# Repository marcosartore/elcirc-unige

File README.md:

# elcirc-unige
This repository contains public domain contents of the Electronics and Circuits Ph.D. course @UniGe held by Marco Sartore.

The folder "analog-pid" contains the Kicad project of an Analog PID (Proportional Integral Derivative) controller.
Production files are in the "gerber" subfolder.

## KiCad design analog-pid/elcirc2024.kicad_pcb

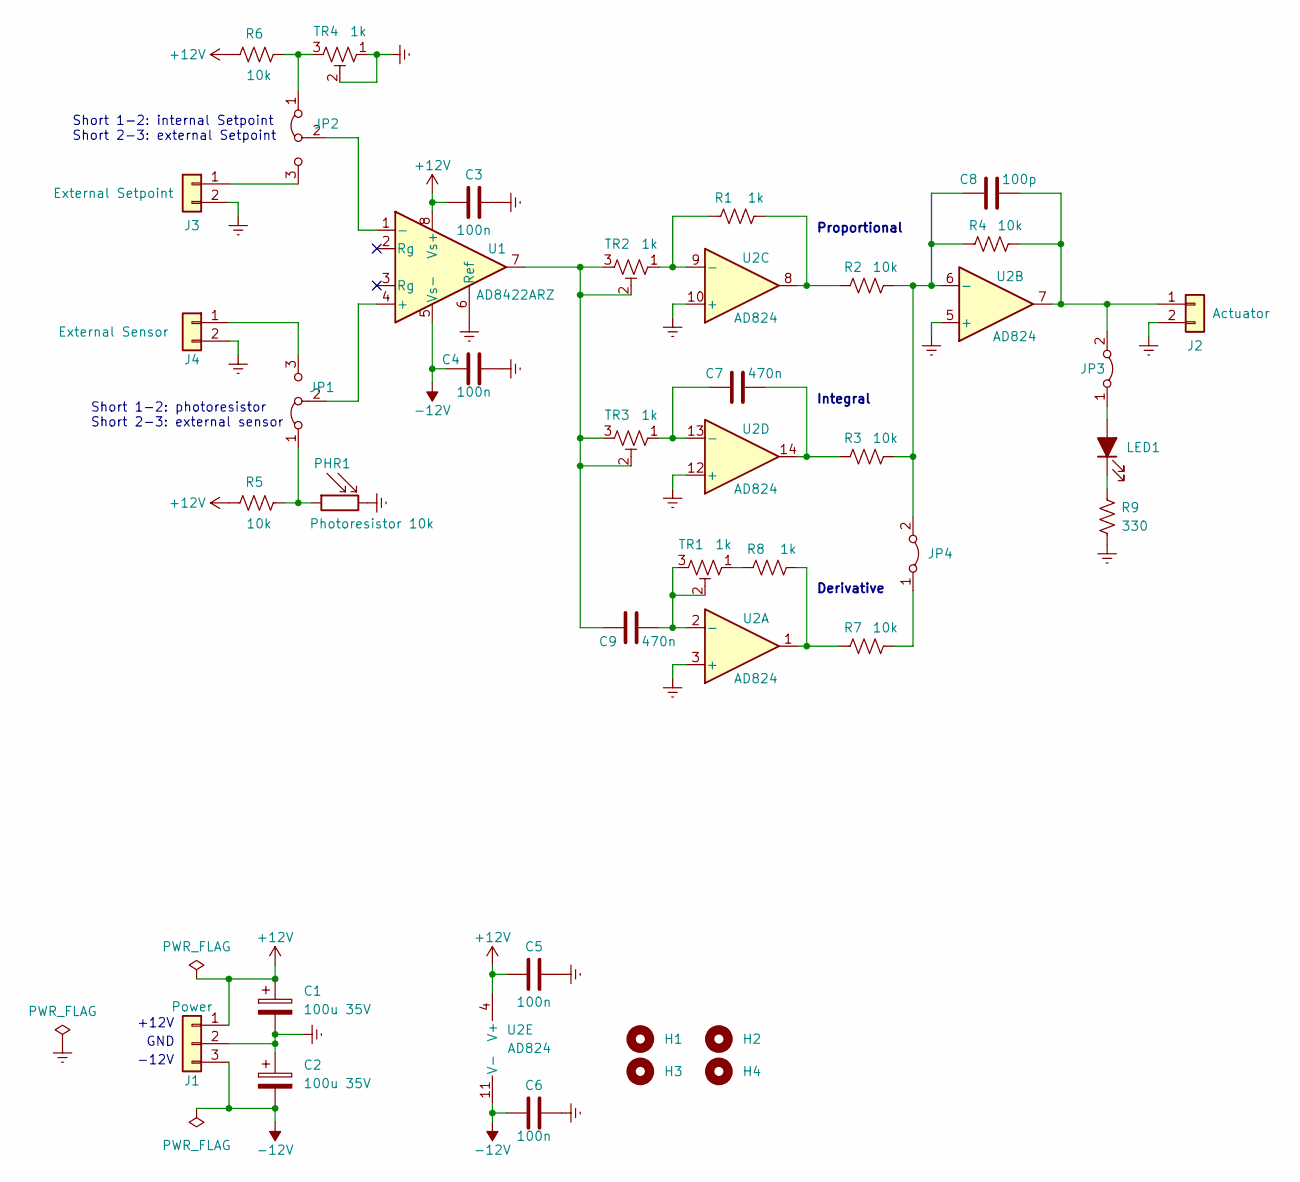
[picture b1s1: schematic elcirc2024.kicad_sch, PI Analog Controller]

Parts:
C1, C2: 100u 35V; CP_Elec_6.3x7.7
C3, C4, C5, C6: 100n; C_0805_2012Metric_Pad1.18x1.45mm_HandSolder
C7, C9: 470n; C_0805_2012Metric_Pad1.18x1.45mm_HandSolder
C8: 100p; C_0805_2012Metric_Pad1.18x1.45mm_HandSolder
H1, H2, H3, H4: MountingHole; MountingHole_3.2mm_M3
J1: Power; TerminalBlock_Phoenix_PT-1,5-3-3.5-H_1x03_P3.50mm_Horizontal; Digikey A112369-ND
J2: Actuator; conn_TE_282834-2; Digikey A98333-ND
J3: External Setpoint; conn_TE_282834-2; Digikey A98333-ND
J4: External Sensor; conn_TE_282834-2; Digikey A98333-ND
JP1, JP2: Jumper_3_Bridged12; PinHeader_1x03_P2.54mm_Vertical
JP3, JP4: Jumper_2_Bridged; PinHeader_1x02_P2.54mm_Vertical
LED1: LED_Filled; LED_D5.0mm
PHR1: Photoresistor 10k; photoresistor_NSL-5152
R1, R8: 1k; R_0805_2012Metric_Pad1.20x1.40mm_HandSolder
R2, R3, R4, R5, R6, R7: 10k; R_0805_2012Metric_Pad1.20x1.40mm_HandSolder
R9: 330; R_0805_2012Metric_Pad1.20x1.40mm_HandSolder
TR1, TR2, TR3, TR4: 1k; Potentiometer_Bourns_3296W_Vertical
U1: AD8422ARZ; SOIC-8_3.9x4.9mm_P1.27mm
U2: AD824; SOIC-14_3.9x8.7mm_P1.27mm

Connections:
+12V: C1.1, C3.1, C5.1, J1.1, R5.2, R6.2, U1.8 (Vs+), U2.4 (V+)
-12V: C2.2, C4.1, C6.1, J1.3, U1.5 (Vs-), U2.11 (V-)
GNDREF: C1.2, C2.1, C3.2, C4.2, C5.2, C6.2, J1.2, J2.2, J3.2, J4.2, PHR1.2, R9.1, TR4.1, TR4.2, U1.6 (Ref), U2.3 (+), U2.5 (+), U2.10 (+), U2.12 (+)
unnamed: C7.2, R3.1, U2.14
unnamed: C9.1, TR2.2, TR2.3, TR3.2, TR3.3, U1.7
unnamed: C8.2, J2.1, JP3.2 (B), R4.2, U2.7
unnamed: J3.1, JP2.3 (B)
unnamed: J4.1, JP1.3 (B)
unnamed: JP1.1 (A), PHR1.1, R5.1
unnamed: JP1.2 (C), U1.4 (+)
unnamed: JP2.1 (A), R6.1, TR4.3
unnamed: JP2.2 (C), U1.1 (-)
unnamed: JP3.1 (A), LED1.2 (A)
unnamed: JP4.1 (A), R7.2
unnamed: C8.1, JP4.2 (B), R2.2, R3.2, R4.1, U2.6 (-)
unnamed: LED1.1 (K), R9.2
unnamed: R1.2, R2.1, U2.8
unnamed: R7.1, R8.2, U2.1
unnamed: R8.1, TR1.1
unnamed: C9.2, TR1.2, TR1.3, U2.2 (-)
unnamed: R1.1, TR2.1, U2.9 (-)
unnamed: C7.1, TR3.1, U2.13 (-)

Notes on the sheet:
Short 1-2: internal Setpoint Short 2-3: external Setpoint
Integral
GND
Derivative
+12V
Short 1-2: photoresistor Short 2-3: external sensor
-12V
Proportional

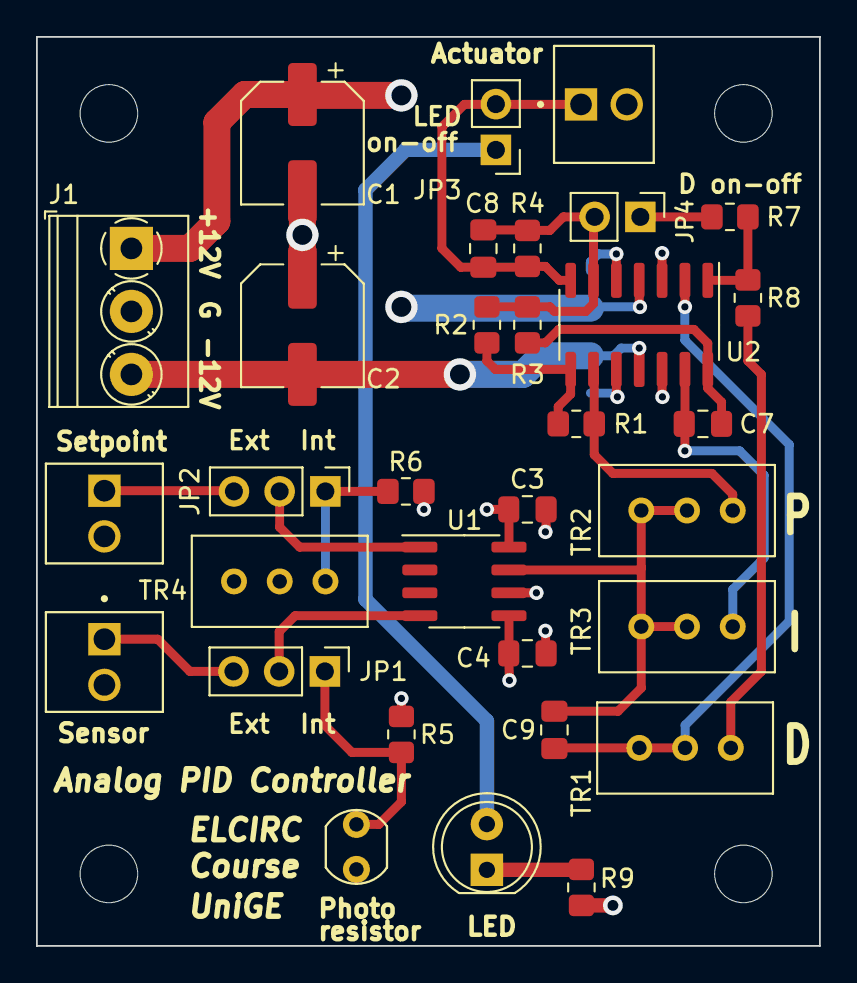
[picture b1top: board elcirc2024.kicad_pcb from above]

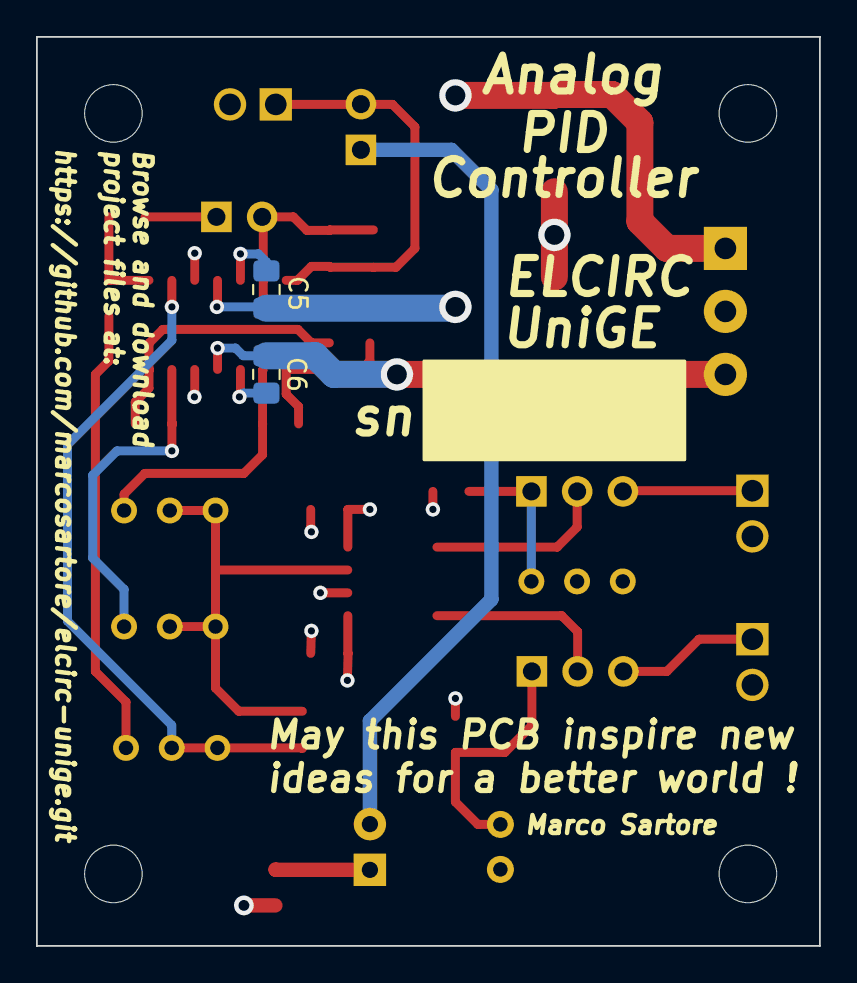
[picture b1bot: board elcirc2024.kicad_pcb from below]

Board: 4 copper layers, 43.5 x 50.5 mm, 38 parts (2 on the bottom side), 22 nets.

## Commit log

2024-03-09 Added analog PID Kicad project
2024-03-09 Added the analog PID Kicad project
2024-03-09 Edited readme file
2024-03-09 added tmp file
2024-03-09 Create LICENSE
